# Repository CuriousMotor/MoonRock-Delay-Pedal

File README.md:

# MoonRock-Delay-Pedal
A PCB for simple PT2399 based delay effect guitar pedal based on Boy In Well.

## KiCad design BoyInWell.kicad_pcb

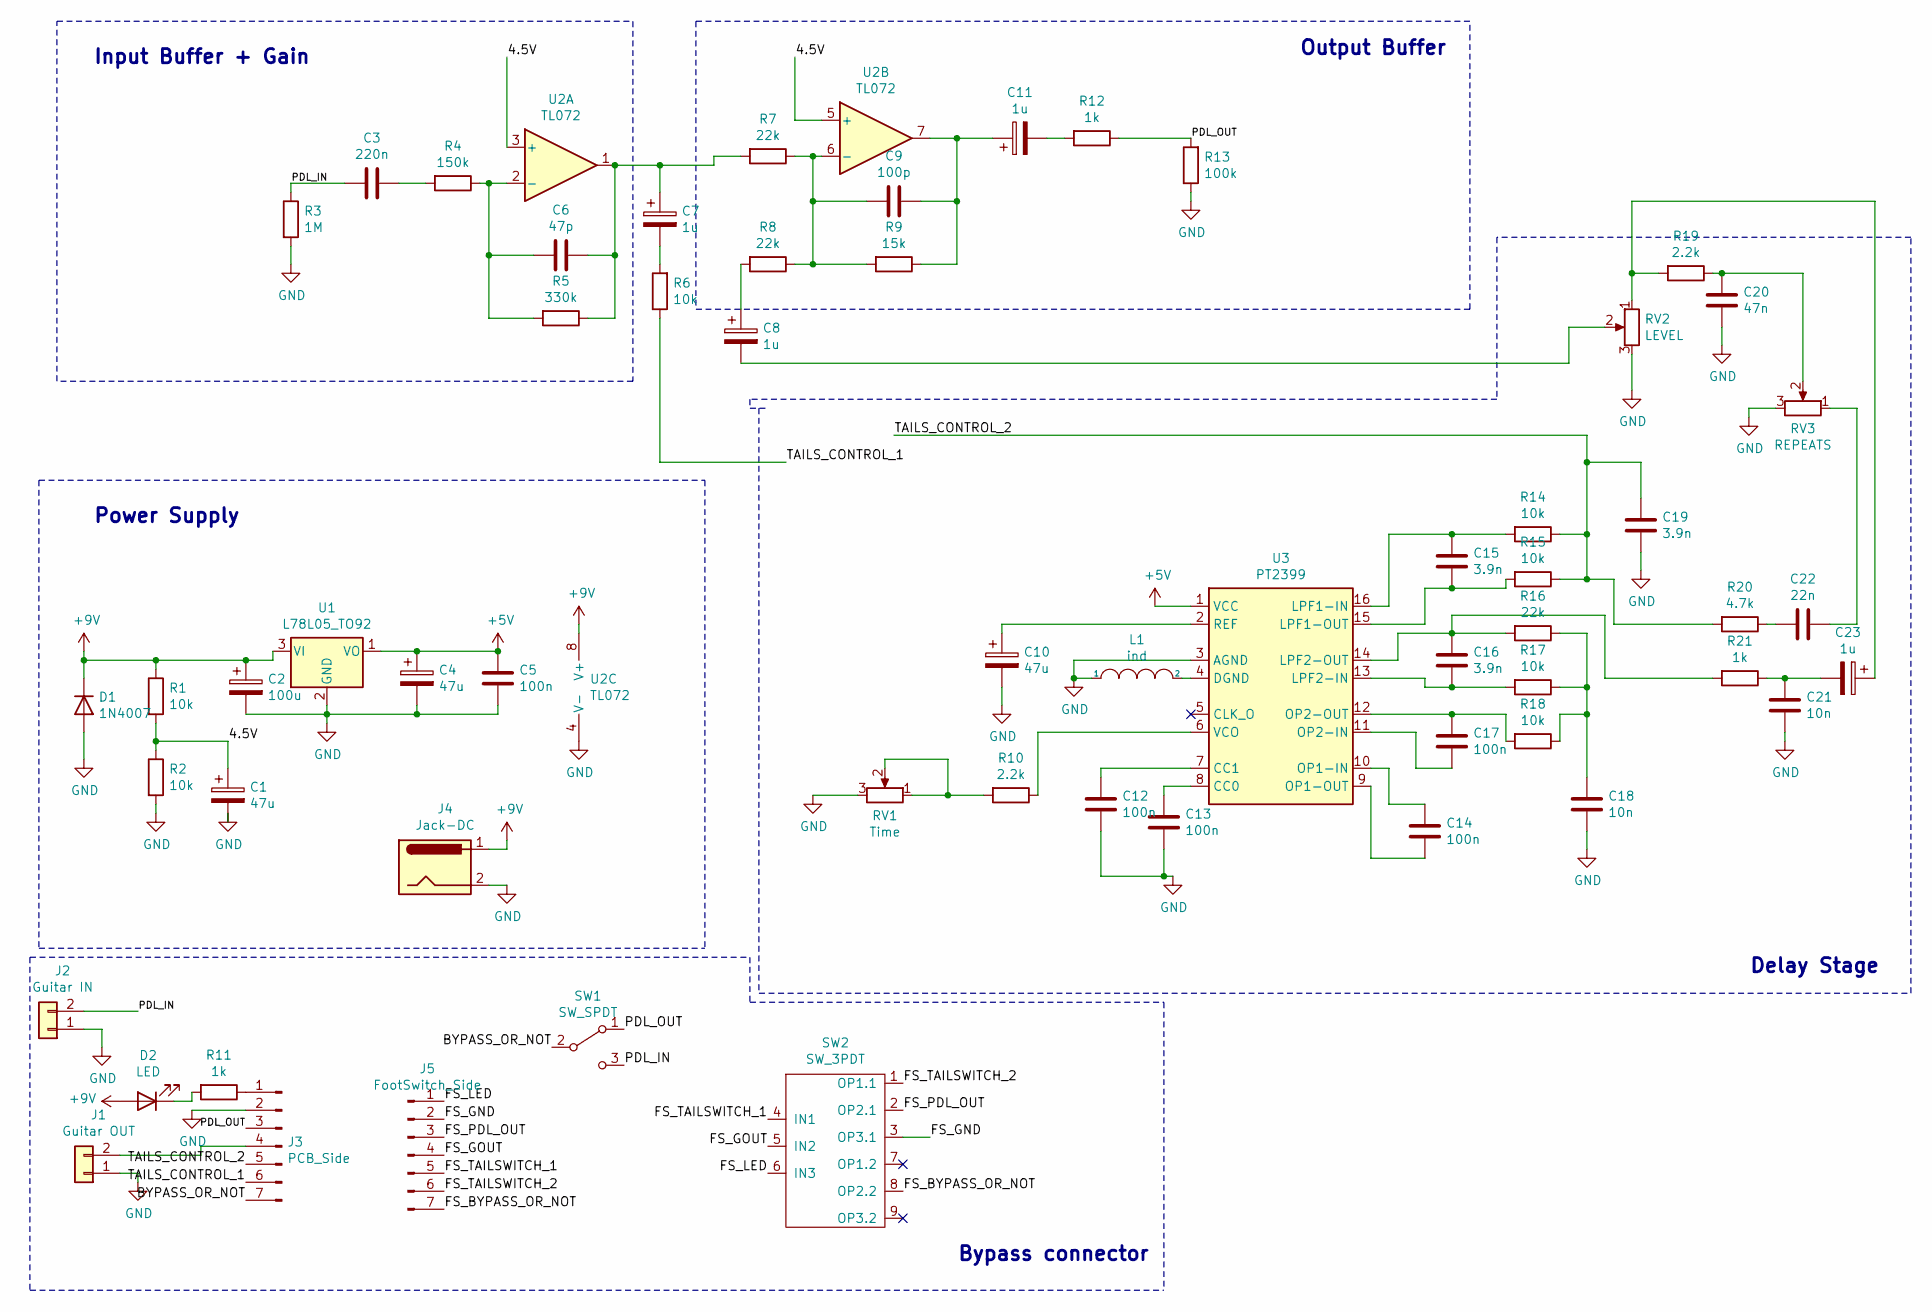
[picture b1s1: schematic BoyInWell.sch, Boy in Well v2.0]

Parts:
C1, C4, C10: 47u; CP_Radial_D5.0mm_P2.50mm
C2: 100u; CP_Radial_D6.3mm_P2.50mm
C3: 220n; C_Rect_L10.0mm_W3.0mm_P7.50mm_FKS3_FKP3
C5, C12, C13, C14, C17: 100n; C_Rect_L9.0mm_W2.6mm_P7.50mm_MKT
C6: 47p; C_Disc_D7.5mm_W2.5mm_P5.00mm
C7, C8, C11, C23: 1u; CP_Radial_D5.0mm_P2.50mm
C9: 100p; C_Disc_D5.0mm_W2.5mm_P2.50mm
C15, C16, C19: 3.9n; C_Rect_L4.6mm_W2.0mm_P2.50mm_MKS02_FKP02
C18, C21: 10n; C_Rect_L4.6mm_W3.0mm_P2.50mm_MKS02_FKP02
C20: 47n; C_Rect_L7.2mm_W3.0mm_P5.00mm_FKS2_FKP2_MKS2_MKP2
C22: 22n; C_Rect_L4.6mm_W2.0mm_P2.50mm_MKS02_FKP02
D1: 1N4007; D_DO-35_SOD27_P10.16mm_Horizontal
D2: LED; LED_D5.0mm
J1: Guitar OUT; PinHeader_1x02_P2.54mm_Vertical
J2: Guitar IN; PinHeader_1x02_P2.54mm_Vertical
J3: PCB_Side; PinHeader_1x07_P2.54mm_Vertical
J4: Jack-DC; BarrelJack_Horizontal
J5: FootSwitch_Side; PinHeader_1x07_P2.54mm_Vertical
L1: ind; L_Axial_L6.6mm_D2.7mm_P10.16mm_Horizontal_Vishay_IM-2
R1, R2, R6, R14, R15, R17, R18: 10k; R_Axial_DIN0207_L6.3mm_D2.5mm_P7.62mm_Horizontal
R3: 1M; R_Axial_DIN0207_L6.3mm_D2.5mm_P7.62mm_Horizontal
R4: 150k; R_Axial_DIN0207_L6.3mm_D2.5mm_P7.62mm_Horizontal
R5: 330k; R_Axial_DIN0207_L6.3mm_D2.5mm_P7.62mm_Horizontal
R7, R8, R16: 22k; R_Axial_DIN0207_L6.3mm_D2.5mm_P7.62mm_Horizontal
R9: 15k; R_Axial_DIN0207_L6.3mm_D2.5mm_P7.62mm_Horizontal
R10, R19: 2.2k; R_Axial_DIN0207_L6.3mm_D2.5mm_P7.62mm_Horizontal
R11, R12, R21: 1k; R_Axial_DIN0207_L6.3mm_D2.5mm_P7.62mm_Horizontal
R13: 100k; R_Axial_DIN0207_L6.3mm_D2.5mm_P7.62mm_Horizontal
R20: 4.7k; R_Axial_DIN0207_L6.3mm_D2.5mm_P7.62mm_Horizontal
RV1: Time; Potentiometer_Omeg_PC16BU_Vertical
RV2: LEVEL; Potentiometer_Omeg_PC16BU_Vertical
RV3: REPEATS; Potentiometer_Omeg_PC16BU_Vertical
SW1: SW_SPDT; SPDT_Toggle
SW2: SW_3PDT; SW_3PDT_STOMP
U1: L78L05_TO92; TO-92_Inline
U2: TL072; DIP-8_W10.16mm
U3: PT2399; DIP-16_W7.62mm

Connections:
+5V: C4.1, C5.1, U1.1 (VO), U3.1 (VCC)
+9V: C2.1, D1.1 (K), D2.2 (A), J4.1, R1.1, U1.3 (VI), U2.8 (V+)
/4.5V: C1.1, R1.2, R2.1, U2.3 (+), U2.5 (+)
/BYPASS_OR_NOT: J3.7, SW1.2 (B)
/FS_BYPASS_OR_NOT: J5.7, SW2.8 (OP2.2)
/FS_GND: J5.2, SW2.3 (OP3.1)
/FS_GOUT: J5.4, SW2.5 (IN2)
/FS_LED: J5.1, SW2.6 (IN3)
/FS_PDL_OUT: J5.3, SW2.2 (OP2.1)
/FS_TAILSWITCH_1: J5.5, SW2.4 (IN1)
/FS_TAILSWITCH_2: J5.6, SW2.1 (OP1.1)
/PDL_IN: C3.2, J2.2, R3.1, SW1.3 (C)
/PDL_OUT: J3.3, R12.1, R13.2, SW1.1 (A)
/TAILS_CONTROL_1: J3.6, R6.1
/TAILS_CONTROL_2: C19.1, J3.5, R14.1, R15.1, R20.2
GND: C1.2, C2.2, C4.2, C5.2, C10.2, C12.2, C13.2, C18.2, C19.2, C20.2, C21.2, D1.2 (A), J1.1, J2.1, J3.2, J4.2, L1.1, R2.2, R3.2, R13.1, RV1.3, RV2.3, RV3.3, U1.2 (GND), U2.4 (V-), U3.3 (AGND)
unnamed: C3.1, R4.2
unnamed: C6.1, C7.1, R5.1, R7.2, U2.1
unnamed: C6.2, R4.1, R5.2, U2.2 (-)
unnamed: C7.2, R6.2
unnamed: C8.1, R8.2
unnamed: C8.2, RV2.2
unnamed: C9.2, R7.1, R8.1, R9.2, U2.6 (-)
unnamed: C10.1, U3.2 (REF)
unnamed: C9.1, C11.1, R9.1, U2.7
unnamed: C11.2, R12.2
unnamed: C12.1, U3.7 (CC1)
unnamed: C13.1, U3.8 (CC0)
unnamed: C14.1, U3.10 (OP1-IN)
unnamed: C14.2, U3.9 (OP1-OUT)
unnamed: C15.1, R14.2, U3.16 (LPF1-IN)
unnamed: C15.2, R15.2, U3.15 (LPF1-OUT)
unnamed: C16.1, R16.2, R21.2, U3.14 (LPF2-OUT)
unnamed: C16.2, R17.2, U3.13 (LPF2-IN)
unnamed: C17.1, R18.2, U3.12 (OP2-OUT)
unnamed: C17.2, U3.11 (OP2-IN)
unnamed: C18.1, R16.1, R17.1, R18.1
unnamed: C20.1, R19.1, RV3.2
unnamed: C21.1, C23.2, R21.1
unnamed: C22.1, RV3.1
unnamed: C22.2, R20.1
unnamed: C23.1, R19.2, RV2.1
unnamed: D2.1 (K), R11.2
unnamed: J1.2, J3.4
unnamed: J3.1, R11.1
unnamed: L1.2, U3.4 (DGND)
unnamed: R10.1, U3.6 (VCO)
unnamed: R10.2, RV1.1, RV1.2

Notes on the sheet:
Input Buffer + Gain
Output Buffer
Power Supply
Delay Stage
Bypass connector

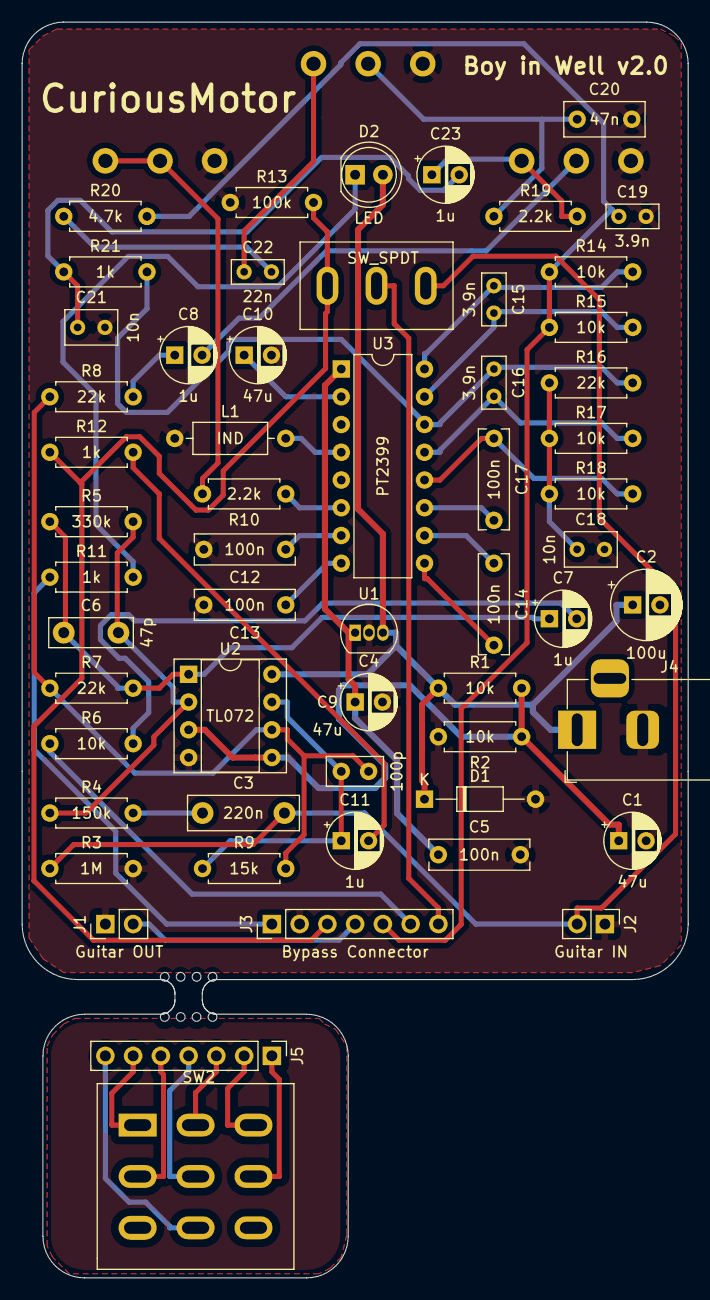
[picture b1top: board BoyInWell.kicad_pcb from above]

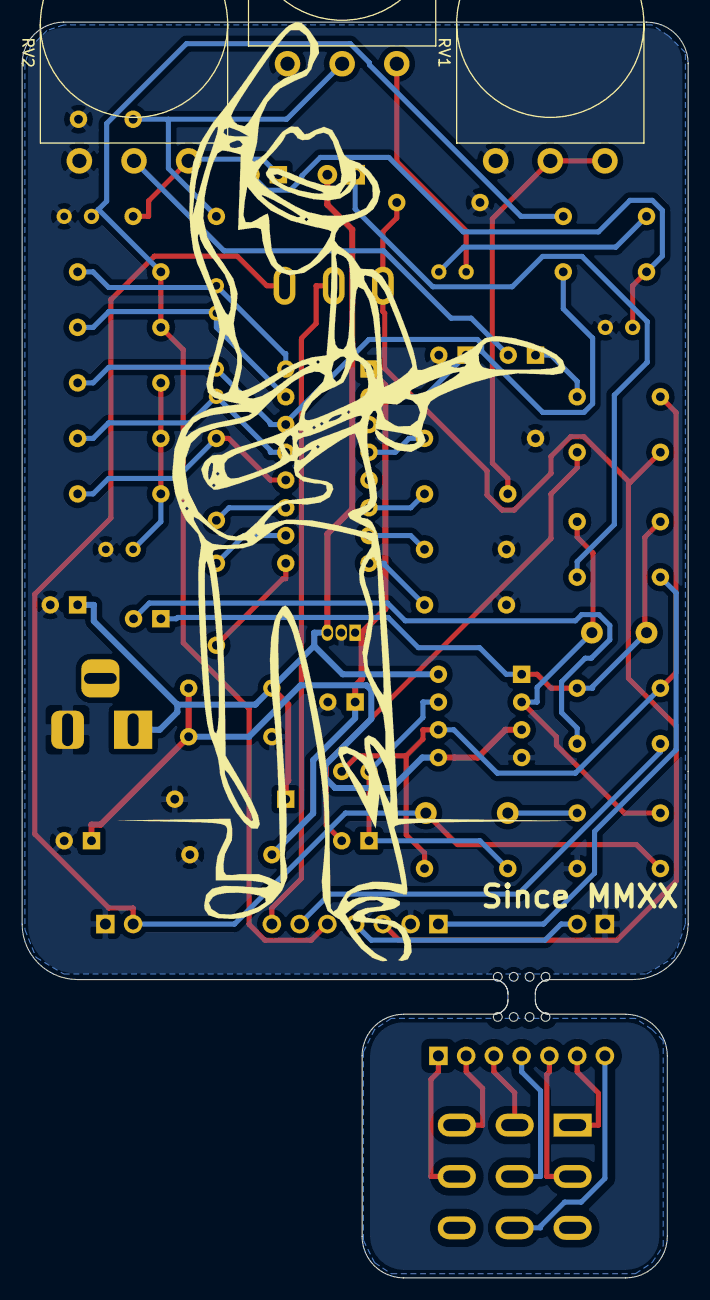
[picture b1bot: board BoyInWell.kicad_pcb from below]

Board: 2 copper layers, 61.0 x 114.9 mm, 62 parts (3 on the bottom side), 48 nets.

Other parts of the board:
mousebites: mousebites; holes
mousebitesX: mousebites; holes
